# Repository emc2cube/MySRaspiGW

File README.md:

MySRaspiGW
==========

Description
-----------

[MySensors](http://www.mysensors.org) SMD gateway (nRF24L01, 2.4GHz) designed to fit Raspberry Pi GPIO ports.
This is the SMD shrunk version of GertSanders [Raspberry Pi2 GPIO interface for NRF24L01+](https://www.openhardware.io/view/17/Raspberry-Pi2-GPIO-interface-for-NRF24L01).

Ordering and options
--------

Four different models are available, differences being the radio used (standard or PA+LNA modules) and the PCB shape.

### Standard nRF24L01 module version:
- Regular version is the smallest form factor available. Radio module is straight with GPIO pins.

- Pimoroni version is designed to fit inside the popular [Pimoroni](http://pimoroni.com) cases designed for the original Raspberry Pi model B, such as [Pibow](https://www.raspberrypi.org/blog/pibow/).

The regular version can be [ordered directly assembled](https://www.openhardware.io/order/105/ASMBL1X) ($20) on [openhardware.io](https://www.openhardware.io/view/105/MySRaspiGW)

Gerber files are included for both versions so you can order these PCB at your favorite PCB fab house and solder the few components yourself.
For an easy ordering process you can directly order these PCB without having to do anything else:
- Regular PCB, [PCBs.io](https://pcbs.io/share/rp2W3) 4 for $0.89, black 1.6mm PCB, ENIG finish or [OSHPark.com](https://oshpark.com/shared_projects/dWrubL3S) 3 for $1.10, purple 1.6mm PCB, ENIG finish.
- Pimoroni PCB, [PCBs.io](https://pcbs.io/share/rN3VE) 4 for $1.20, black 1.6mm PCB, ENIG finish [OSHPark.com](https://oshpark.com/shared_projects/6JsJqI3E) 3 for $1.50, purple 1.6mm PCB, ENIG finish.

### Amplified nRF24L01 PA+LNA module version:
- Regular version is the smallest form factor available. Radio module is straight with GPIO pins.

- Pimoroni version is designed to fit inside the popular [Pimoroni](http://pimoroni.com) cases designed for the original Raspberry Pi model B, such as [Pibow](https://www.raspberrypi.org/blog/pibow/).

The regular version can be [ordered directly assembled](https://www.openhardware.io/order/116/ASMBL1X) ($21) on [openhardware.io](https://www.openhardware.io/view/116/MySRaspiGW-PALNA)

Gerber files are included for both versions so you can order these PCB at your favorite PCB fab house and solder the few components yourself.
For an easy ordering process you can directly order these PCB without having to do anything else:
- Regular PCB, [PCBs.io](https://pcbs.io/share/4Q7e1) 4 for $0.86, black 1.6mm PCB, ENIG finish or [OSHPark.com](https://oshpark.com/shared_projects/PaP5y1X2) 3 for $1.05, purple 1.6mm PCB, ENIG finish.
- Pimoroni PCB, [PCBs.io](https://pcbs.io/share/4o2WQ) 4 for $1.15, black 1.6mm PCB, ENIG finish or [OSHPark.com](https://oshpark.com/shared_projects/2UrzYLvi) 3 for $1.40, purple 1.6mm PCB, ENIG finish.

Installation
-------

Plug the Gateway module to Raspberry Pi Pins 17 to 24 and follow the instructions on [MySensors website](https://www.mysensors.org/build/raspberry) to compile the code.
- If you are using a PA+LNA module and are experiencing some Tx errors add **--my-rf24-pa-level=RF24_PA_LOW** option to your ./configure
- V1.1: For IRQ pin support add **--my-rf24-irq-pin=18** option to your ./configure
- To be sure your pty device is easily identified by any controller use a ttyUSB name, for example add **--my-serial-pty=/dev/ttyUSBMySensorsGateway** option to your ./configure

### Serial interface (pty)
./configure --my-gateway=serial --my-serial-is-pty --my-serial-pty=/dev/ttyUSBMySensorsGateway --my-rf24-pa-level=RF24_PA_LOW --my-rf24-irq-pin=18

### Ethernet interface
./configure --my-rf24-pa-level=RF24_PA_LOW --my-rf24-irq-pin=18

Revision history
----------------

- Version 1.1: IRQ pin support.
- Version 1.0: Initial release.

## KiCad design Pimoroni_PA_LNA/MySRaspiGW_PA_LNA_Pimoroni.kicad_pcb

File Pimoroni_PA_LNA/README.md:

MySRaspiGW
==========

Description
-----------

[MySensors](http://www.mysensors.org) SMD gateway (nRF24L01 PA+LNA, 2.4GHz) designed to fit Raspberry Pi B GPIO ports inside a Pimoroni enclosure.
Shrunk PA+LNA SMD version of GertSanders [Raspberry Pi2 GPIO interface for NRF24L01+](https://www.openhardware.io/view/17/Raspberry-Pi2-GPIO-interface-for-NRF24L01).

Ordering and options
--------

Two different models are available, only difference being the PCB shape.

This is the Pimoroni version, designed to fit inside the popular [Pimoroni](http://pimoroni.com) cases designed for the original Raspberry Pi model B, such as [Pibow](https://www.raspberrypi.org/blog/pibow/).

A [Regular version](https://www.github.com/emc2cube/MySRaspiGW/tree/master/Regular_PA_LNA/) is also available. It has a smaller form factor with radio module being straight with GPIO pins. It should fit most of the other raspberry Pi model B cases, and any other recent model.

Gerber files are included so you can order these PCB at your favorite PCB fab house and solder the few components yourself.
For an easy ordering process you can directly order these PCB without having to do anything else:
- [PCBs.io](https://pcbs.io/share/4o2WQ) 4 for $1.15, black 1.6mm PCB, ENIG finish.
- [OSHPark.com](https://oshpark.com/shared_projects/2UrzYLvi) 3 for $1.40, purple 1.6mm PCB, ENIG finish.

Installation
-------

Plug the Gateway module to Raspberry Pi Pins 17 to 24 and follow the instructions on [MySensors website](https://www.mysensors.org/build/raspberry) to compile the code.
- If you are using a PA+LNA module and are experiencing some Tx errors add **--my-rf24-pa-level=RF24_PA_LOW** option to your ./configure
- V1.1: For IRQ pin support add **--my-rf24-irq-pin=18** option to your ./configure
- To be sure your pty device is easily identified by any controller use a ttyUSB name, for example add **--my-serial-pty=/dev/ttyUSBMySensorsGateway** option to your ./configure

### Serial interface (pty)
./configure --my-gateway=serial --my-serial-is-pty --my-serial-pty=/dev/ttyUSBMySensorsGateway --my-rf24-pa-level=RF24_PA_LOW --my-rf24-irq-pin=18

### Ethernet interface
./configure --my-rf24-pa-level=RF24_PA_LOW --my-rf24-irq-pin=18

Revision history
----------------

- Version 1.1: IRQ pin support.
- Version 1.0: Initial release.

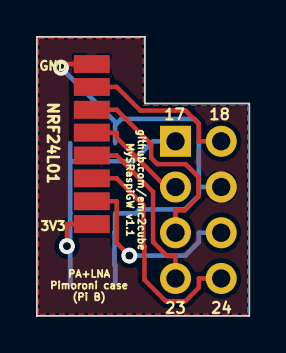
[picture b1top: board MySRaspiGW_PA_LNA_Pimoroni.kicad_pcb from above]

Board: 2 copper layers, 11.8 x 15.5 mm, 5 parts (0 on the bottom side), 8 nets.

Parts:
C1: 0.1µF; C_0805_HandSoldering
C2: 4.7µF; C_0805_HandSoldering
C3: 47µF; C_0805_HandSoldering
P1: CONN_02X04; Socket_Strip_Straight_2x04
U1: NRF24L01; NRF24L01_PA_LNA-SMD

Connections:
+3V3: C1.1, C2.1, C3.1, P1.1, U1.2
CE: P1.6, U1.3
CSN: P1.8, U1.4
GND: C1.2, C2.2, C3.2, P1.4, U1.1
IRQ: P1.2, U1.8
MISO: P1.5, U1.7
MOSI: P1.3, U1.6
SCK: P1.7, U1.5

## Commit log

2016-05-30 Initial release
    Initial release
2016-06-17 Pictures and ordering infos
    Adding pictures and updated ordering infos
2016-07-04 Add PA+LNA version
    Release of a nRF24L01 PA+LNA SMD version of the gateway.
    Surprisingly working despite having a high power usage. Use with
    caution, risk of frying your GPIO ports.
2016-07-07 Updated openhardware.io infos
    Updated openhardware.io infos
2016-11-23 MySensors V2.0 update
    Arduino code updated to be compatible with MySensors V2.0 update
2017-03-27 v1.1 IRQ support
    Added IRQ support on pin 18
2017-03-27 MD fixes
    Cosmetic changes
2017-05-08 Readme update
